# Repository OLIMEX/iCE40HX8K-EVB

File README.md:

# iCE40HX8K-EVB
iCE40HX8K development board with SRAM and bus for fast ADC, DAC, IOs

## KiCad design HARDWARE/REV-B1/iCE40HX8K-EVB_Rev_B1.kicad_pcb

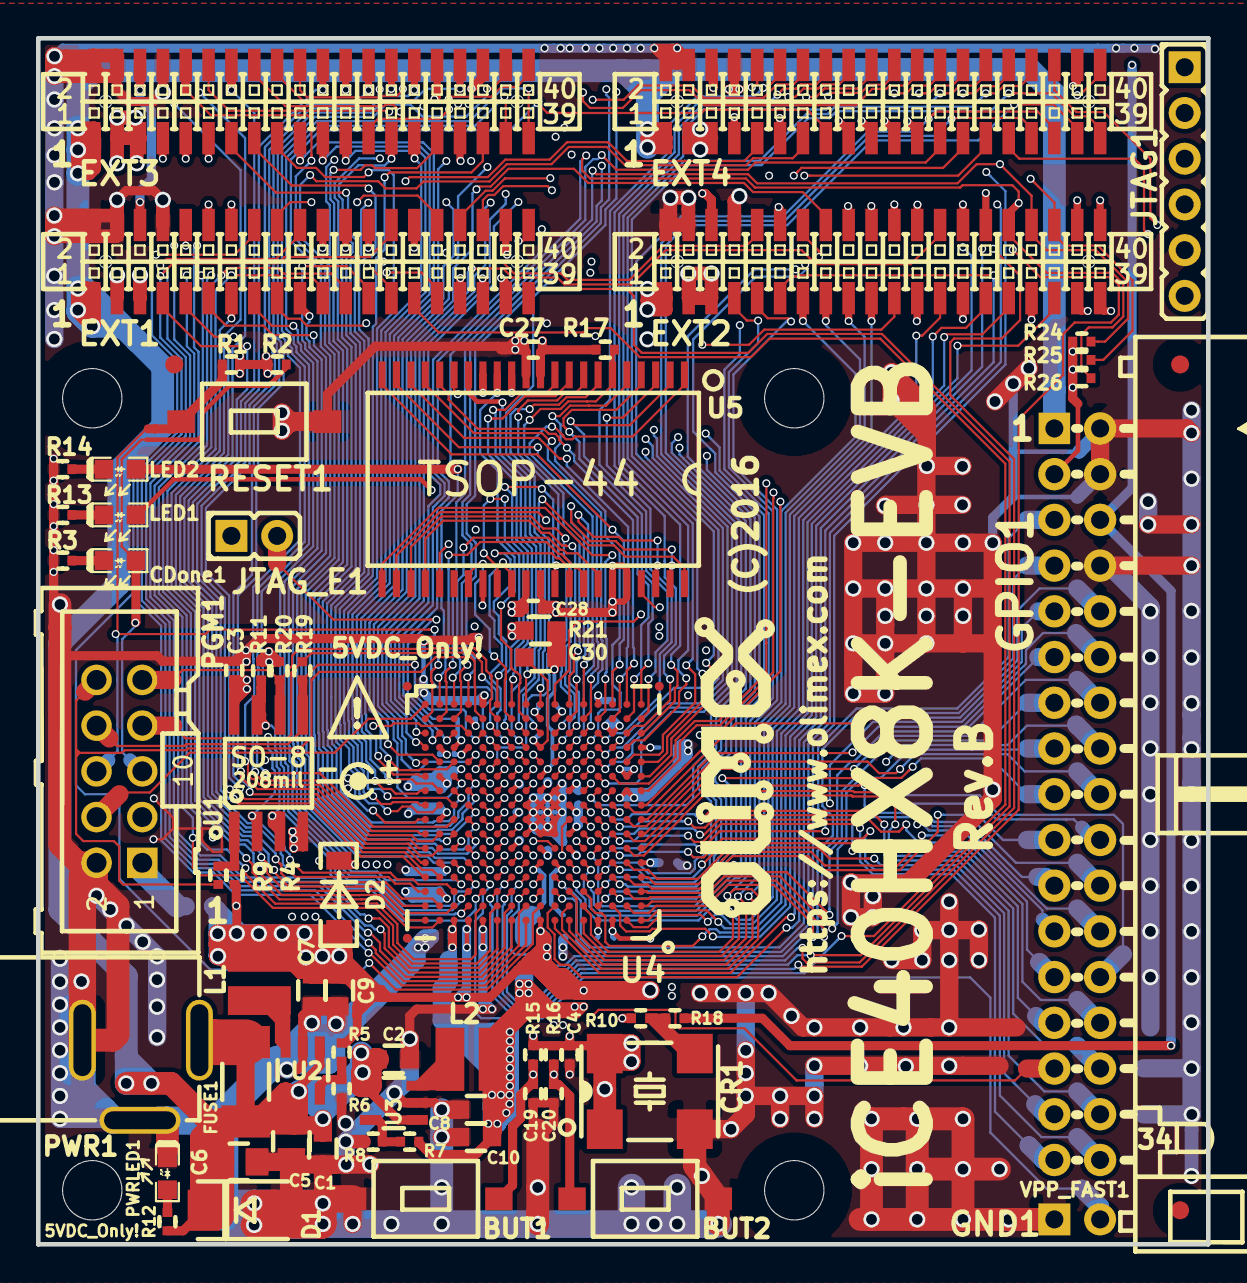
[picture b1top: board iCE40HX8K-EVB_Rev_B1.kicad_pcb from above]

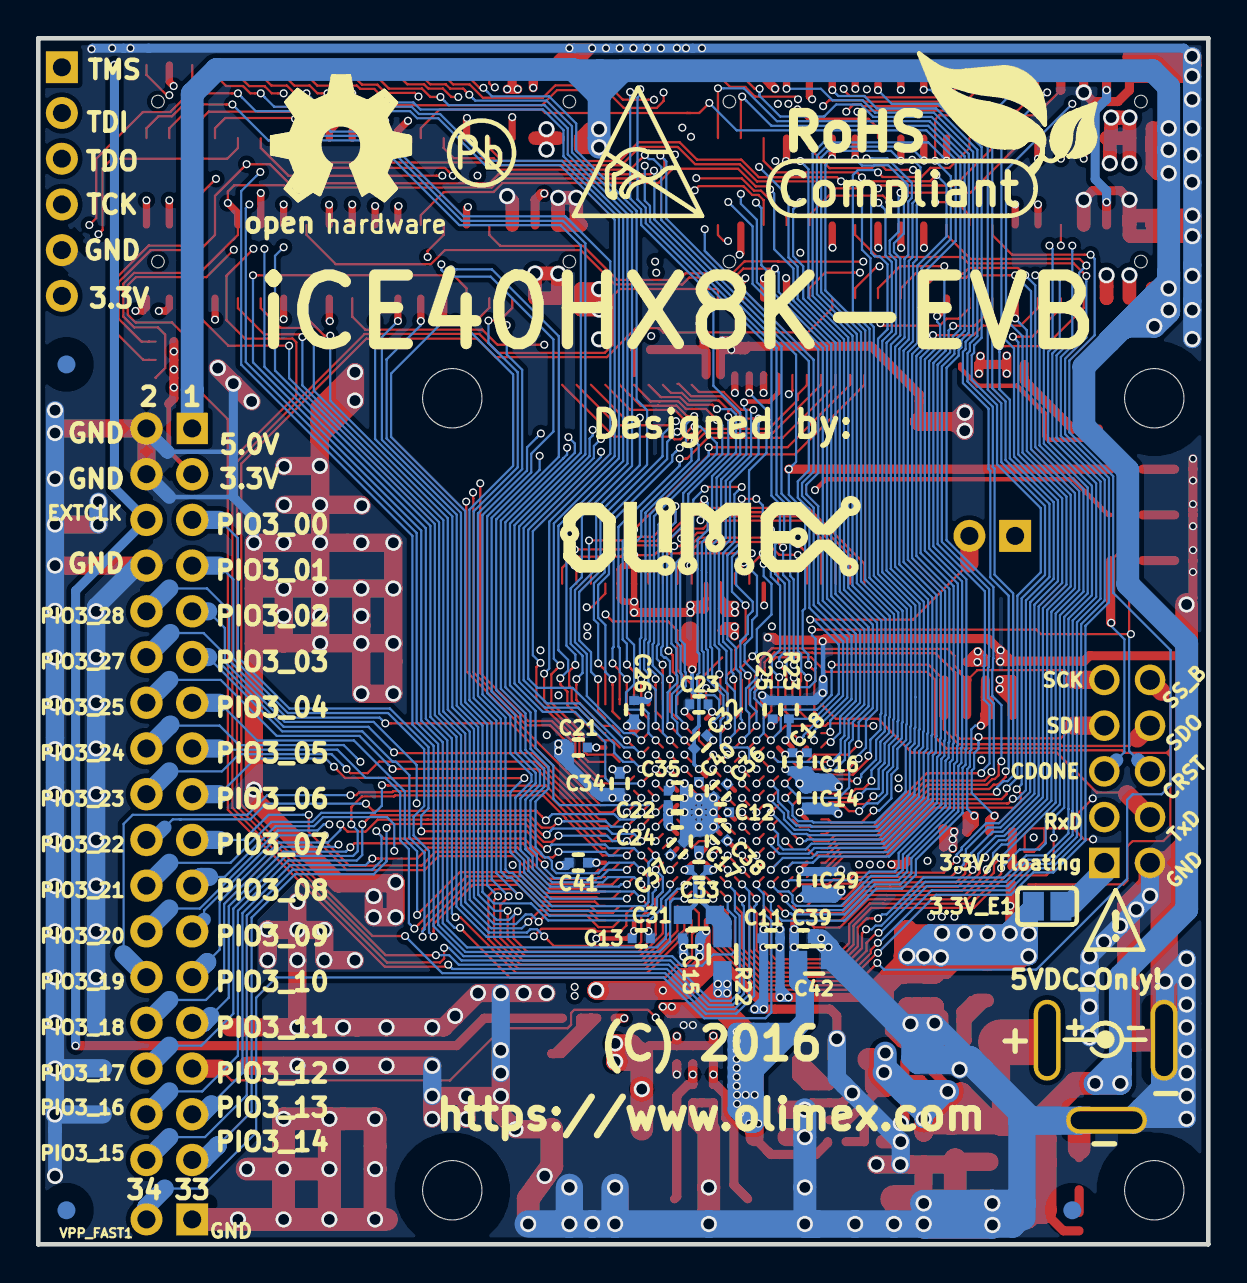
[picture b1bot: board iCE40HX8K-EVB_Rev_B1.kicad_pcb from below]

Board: 4 copper layers, 65.0 x 67.0 mm, 104 parts (32 on the bottom side), 232 nets.

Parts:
3.3V_E1: Opened; SJ
BUT1, BUT2: T1107A(6x3,8x2,5MM)
C1, C2, C7, C8, C9, C10, C30, C31, C42: 22uF/6.3V/20%/X5R; C_0603_5MIL_DWS
C3, C4, C11, C12, C13, C14, C15, C16, C17, C18, C21, C22, C23, C24, C25, C26, C27, C28, C29, C32, C33, C34, C35, C36, C37, C38, C39, C40, C41: 100nF/50V/20%/Y5V; C_0402_5MIL_DWS
C5, C6: 47uF/6.3V/20%/X5R; C_0805_5MIL_DWS
C19, C20: NA(100nF/50V/20%/Y5V); C_0402_5MIL_DWS
CDone1: LED/Green/0603; LED_0603_KA
CR1: Oscillator-100MHZ_TXC-7W; Oscillator_7.0x5.0mm
D1: SMBJ6.0A(DO-214AA); DO214AA_1(K)-2(A)
D2: 1N5819(S4SOD-123); SOD-123_1C-2A_KA
EXT1, EXT2, EXT3, EXT4: PA-V16X-2X20-LF; GPH127SMT-02X20(PA-V16X-2X20-LF)
FUSE1: NA(5025); FUSE-5025
GND1: TESTPAD; TEST_PAD40x70_SQUARE
GPIO1: BH34R
JTAG1: NA(HN1x6); HN1x6
JTAG_E1: NA(HN1x2(Opened)); HN1x2
L1, L2: 2.2uH/1.5A/DCR<0.1R/CD32; CD32
LED1, LED2: LED/Red/0603; LED_0603_KA
MountingHole: Mounting_hole_3.3mm
MountingHole#2, MountingHole#3, MountingHole#4: Mounting_hole_3.3mm
PGM1: BH10S; UEXT_ML10
PWR1: PWRJ-2mm(YDJ-1134); PWRJ-2mm(YDJ-1136)
PWRLED1: LED/Red/0603; LED_0603_KA
R1, R4, R11, R15, R16, R17, R20, R23: 10k; R_0402_5MIL_DWS
R2, R12, R13, R14: 2.2k; R_0402_5MIL_DWS
R3, R9, R10, R18: 22R; R_0402_5MIL_DWS
R5, R7, R8: 4.99k/1%; R_0402_5MIL_DWS
R6: 1.1k/1%; R_0402_5MIL_DWS
R19: NA(22R); R_0402_5MIL_DWS
R21, R22: 100R; R_0603_5MIL_DWS
R24, R25, R26: NA(10k); R_0402_5MIL_DWS
RESET1: T1107A(6x3,8x2,5MM)
Ref**: Val**; LOGO_ROHS_1
Ref**#2: Val**; LOGO_ANTISTATIC_1
U1: EN25Q16B-104HIP(SOIC-8_208mil); SO-8_208mil
U2, U3: SY8009AAAC(SOT23-5); SOT-23-5
U4: iCE40HX8K-CT256(256-Ball_caBGA); 256-Ball_caBGA(Pitch_0.80mm_Pad_0.40mm)
U5: K6R4016V1D-TC10(TSOP-44); TSOP-44_Pitch-0.80mm_18.80x11.80x1.20mm
VPP_FAST1: TESTPAD; TEST_PAD_40x70_Round

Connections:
+1V2: C8.2, C10.2, C34.2, C35.2, C36.2, C37.2, C38.2, C39.2, C42.1, L2.1, R7.2, R21.2, R22.2, U4.A14, U4.F6, U4.F10, U4.K6, U4.K10, U4.L2
+3V3: 3.3V_E1.2, C3.2, C4.2, C7.2, C9.2, C11.2, C12.2, C13.2, C14.2, C15.2, C16.2, C17.2, C18.1, C21.2, C22.2, C23.2, C24.2, C25.2, C26.2, C27.2, C28.2, C29.2, C40.2, C41.2, CR1.1, CR1.4, D2.2, EXT1.3, EXT1.5, EXT2.3, EXT2.5, EXT3.3, EXT3.5, EXT4.3, EXT4.5, GPIO1.3, JTAG1.6, JTAG_E1.1, L1.1, R1.2, R2.2, R4.2, R5.2, R11.1, R15.2, R16.2, R17.1, R20.2, R24.1, R25.1, R26.1, U1.8, U4.A3, U4.A8, U4.A13, U4.C15, U4.E1, U4.F8, U4.G6, U4.H10, U4.H15, U4.J6, U4.K8, U4.N1, U4.N13, U4.N15, U4.P3, U4.R8, U4.R13, U5.11, U5.33
+5V: C1.2, C2.2, C5.2, C6.2, D1.1, EXT1.1, EXT2.1, EXT3.1, EXT4.1, FUSE1.1, FUSE1.2, GPIO1.1, PWR1.+, R12.1, U2.1, U2.4, U3.1, U3.4
/EXTCLK: EXT1.6, EXT2.6, EXT3.6, EXT4.6, GPIO1.6, R18.1
/PIO0_00: EXT1.7, U4.C14
/PIO0_01: EXT1.9, U4.B15
/PIO0_02: EXT1.11, U4.D13
/PIO0_03: EXT1.13, U4.B14
/PIO0_04: EXT1.15, U4.C12
/PIO0_05: EXT1.17, U4.E11
/PIO0_06: EXT1.19, U4.C13
/PIO0_07: EXT1.21, U4.A16
/PIO0_08: EXT1.23, U4.A15
/PIO0_09: EXT1.25, U4.B13
/PIO0_10: EXT1.27, U4.E10
/PIO0_11: EXT1.29, U4.C11
/PIO0_12: EXT1.31, U4.D11
/PIO0_13: EXT1.33, U4.B12
/PIO0_14: EXT1.35, U4.B10
/PIO0_15: EXT1.37, U4.B11
/PIO0_16: EXT1.39, U4.C10
/PIO0_17: EXT1.40, U4.A10
/PIO0_18: EXT1.38, U4.A11
/PIO0_19: EXT1.36, U4.D10
/PIO0_20: EXT1.34, U4.C9
/PIO0_21: EXT1.32, U4.E9
/PIO0_22: EXT1.30, U4.D9
/PIO0_23: EXT1.28, U4.A9
/PIO0_24: EXT1.26, U4.F9
/PIO0_25: EXT1.24, U4.C8
/PIO0_26: EXT1.22, U4.F7
/PIO0_27: EXT1.20, U4.B9
/PIO0_28: EXT1.18, U4.D8
/PIO0_29: EXT1.16, U4.B8
/PIO0_30: EXT1.14, U4.A7
/PIO0_31: EXT1.12, U4.C7
/PIO0_32: EXT1.10, U4.B7
/PIO0_33: EXT2.7, U4.B6
/PIO0_34: EXT2.9, U4.C6
/PIO0_35: EXT2.11, U4.D7
/PIO0_36: EXT2.13, U4.A6
/PIO0_37: EXT2.15, U4.D6
/PIO0_38: EXT2.17, U4.A5
/PIO0_39: EXT2.19, U4.B5
/PIO0_40: EXT2.21, U4.E6
/PIO0_41: EXT2.23, U4.B4
/PIO0_42: EXT2.25, U4.A2
/PIO0_43: EXT2.27, U4.D5
/PIO0_44: EXT2.29, U4.A1
/PIO0_45: EXT2.31, U4.C5
/PIO0_46: EXT2.33, U4.C4
/PIO0_47: EXT2.35, U4.B3
/PIO0_48: EXT2.37, U4.D4
/PIO0_49: EXT2.39, U4.E5
/PIO0_50: EXT2.40, U4.D3
/PIO0_51: EXT2.38, U4.C3
/PIO1_00: EXT2.36, JTAG1.2, R25.2, U4.R14
/PIO1_01: EXT2.34, JTAG1.1, R24.2, U4.R15
/PIO1_02: EXT2.32, JTAG1.4, R26.2, U4.P14
/PIO1_03: EXT2.30, JTAG1.3, U4.P15
/PIO1_04: EXT2.28, U4.P16
/PIO1_05: EXT2.26, U4.M13
/PIO1_06: EXT2.24, U4.M14
/PIO1_07: EXT2.22, U4.L12
/PIO1_08: EXT2.20, U4.N16
/PIO1_09: EXT2.18, U4.L13
/PIO1_10: EXT2.16, U4.L14
/PIO1_11: EXT2.14, U4.K12
/PIO1_12: EXT2.12, U4.M16
/PIO1_13: EXT2.10, U4.J10
/PIO1_14: EXT3.7, U4.M15
/PIO1_15: EXT3.9, U4.J11
/PIO1_16: EXT3.11, U4.L16
/PIO1_17: EXT3.13, U4.K13
/PIO1_18: EXT3.15, U4.K14
/PIO1_19: EXT3.17, U4.J15
/PIO1_20: EXT3.19, U4.K15
/PIO1_21: EXT3.21, U4.K16
/PIO1_22: EXT3.23, U4.J14
/PIO1_23: EXT3.25, U4.J12
/PIO1_24: EXT3.27, U4.J13
/PIO1_25: EXT3.29, U4.J16
/PIO1_26: EXT3.31, U4.H13
/PIO1_27: EXT3.33, U4.H11
/PIO1_28: EXT3.35, U4.H16
/PIO1_29: EXT3.37, U4.H14
/PIO1_30: EXT3.39, U4.G16
/PIO1_31: EXT3.40, U4.H12
/PIO1_32: EXT3.38, U4.G15
/PIO1_33: EXT3.36, U4.G10
/PIO1_34: EXT3.34, U4.F16
/PIO1_35: EXT3.32, U4.G11
/PIO1_36: EXT3.30, U4.F15
/PIO1_37: EXT3.28, U4.G14
/PIO1_38: EXT3.26, U4.E16
/PIO1_39: EXT3.24, U4.G13
/PIO1_40: EXT3.22, U4.D16
/PIO1_41: EXT3.20, U4.G12
/PIO1_42: EXT3.18, U4.F14
/PIO1_43: EXT3.16, U4.F12
/PIO1_44: EXT3.14, U4.D15
/PIO1_45: EXT3.12, U4.F11
/PIO1_46: EXT3.10, U4.E14
/PIO1_47: EXT4.7, U4.C16
/PIO1_48: EXT4.9, U4.F13
/PIO1_49: EXT4.11, U4.B16
/PIO1_50: EXT4.13, U4.E13
/PIO1_51: EXT4.15, U4.D14
/PIO2_37: EXT4.17, U4.M11
/PIO2_38: EXT4.19, U4.T13
/PIO2_39: EXT4.21, U4.N12
/PIO2_40/RxD: PGM1.3, U4.L11
/PIO2_41/TxD: PGM1.4, U4.T16
/PIO2_42/LED1: EXT4.23, LED1.2, U4.M12
/PIO2_43/LED2: EXT4.25, LED2.2, U4.R16
/PIO2_44/BUT1: BUT1.1, C19.2, R15.1, U4.K11
/PIO2_45/BUT2: BUT2.1, C20.2, R16.1, U4.P13
/PIO3_00/IOL_1A: GPIO1.5, U4.E4
/PIO3_01/IOL_1B: GPIO1.7, U4.B2
/PIO3_02/IOL_2A: GPIO1.9, U4.F5
/PIO3_03/IOL_2B: GPIO1.11, U4.B1
/PIO3_04/IOL_3A: GPIO1.13, U4.C1
/PIO3_05/IOL_3B: GPIO1.15, U4.C2
/PIO3_06/IOL_4A: GPIO1.17, U4.F4
/PIO3_07/IOL_4B: GPIO1.19, U4.D2
/PIO3_08/IOL_5A: GPIO1.21, U4.G5
/PIO3_09/IOL_5B: GPIO1.23, U4.D1
/PIO3_10/IOL_6A: GPIO1.25, U4.G4
/PIO3_11/IOL_6B: GPIO1.27, U4.E3
/PIO3_12/IOL_7A: GPIO1.29, U4.H5
/PIO3_13/IOL_7B: GPIO1.31, U4.E2
/PIO3_14/IOL_8A: GPIO1.33, U4.G3
/PIO3_15/IOL_8B: GPIO1.34, U4.F3
/PIO3_16/IOL_9A: GPIO1.32, U4.H3
/PIO3_17/IOL_9B: GPIO1.30, U4.F2
/PIO3_18/IOL_10A: GPIO1.28, U4.H6
/PIO3_19/IOL_10B: GPIO1.26, U4.F1
/PIO3_20/IOL_11A: GPIO1.24, U4.H4
/PIO3_21/IOL_11B: GPIO1.22, U4.G2
/PIO3_22/IOL_12A: GPIO1.20, U4.J4
/PIO3_23/IOL_12B: GPIO1.18, U4.H2
/PIO3_24/IOL_13A: GPIO1.16, U4.J5
/PIO3_25/IOL_13B: GPIO1.14, U4.G1
/PIO3_27/IOL_14B: GPIO1.12, U4.H1
/PIO3_28/IOL_15A: GPIO1.10, U4.J2
/PIO3_29: EXT4.27, U4.J1
/PIO3_30: EXT4.29, U4.K1
/PIO3_31: EXT4.31, U4.K3
/PIO3_32: EXT4.33, U4.L4
/PIO3_33: EXT4.35, U4.L1
/PIO3_34: EXT4.37, U4.K4
/PIO3_35: EXT4.39, U4.M1
/PIO3_36: EXT4.40, U4.L6
/PIO3_37: EXT4.38, U4.L3
/PIO3_38: EXT4.36, U4.K5
/PIO3_39: EXT4.34, U4.M2
/PIO3_40: EXT4.32, U4.L7
/PIO3_41: EXT4.30, U4.N2
/PIO3_42: EXT4.28, U4.M6
/PIO3_43: EXT4.26, U4.M3
/PIO3_44: EXT4.24, U4.L5
/PIO3_45: EXT4.22, U4.N3
/PIO3_46: EXT4.20, U4.P1
/PIO3_47: EXT4.18, U4.M4
/PIO3_48: EXT4.16, U4.P2
/PIO3_49: EXT4.14, U4.M5
/PIO3_50: EXT4.12, U4.R1
/PIO3_51: EXT4.10, U4.N4
/SA0: U4.N6, U5.1
/SA1: U4.T1, U5.2
/SA2: U4.P4, U5.3
/SA3: U4.R2, U5.4
/SA4: U4.N5, U5.5
/SA5: U4.T2, U5.18
/SA6: U4.P5, U5.19
/SA7: U4.R3, U5.20
/SA8: U4.R5, U5.21
/SA9: U4.T3, U5.22
/SA10: U4.R4, U5.23
/SA11: U4.M7, U5.24
/SA12: U4.N7, U5.25
/SA13: U4.P6, U5.26
/SA14: U4.M8, U5.27
/SA15: U4.T5, U5.42
/SA16: U4.R6, U5.43
/SA17: U4.P8, U5.44
/SD0: U4.T8, U5.7
/SD1: U4.P7, U5.8
/SD2: U4.N9, U5.9
/SD3: U4.T9, U5.10
/SD4: U4.M9, U5.13
/SD5: U4.R9, U5.14
/SD6: U4.K9, U5.15
/SD7: U4.P9, U5.16
/SD8: U4.R10, U5.29
/SD9: U4.L10, U5.30
/SD10: U4.P10, U5.31
/SD11: U4.N10, U5.32
/SD12: U4.T10, U5.35
/SD13: U4.T11, U5.36
/SD14: U4.T15, U5.37
/SD15: U4.T14, U5.38
/SRAM_#CS: R17.2, U4.T6, U5.6
/SRAM_#OE: U4.L9, U5.41
/SRAM_#WE: U4.T7, U5.17
/SYSCLK: R10.1, U4.J3
/TRST_B: JTAG_E1.2, R23.1, U4.N14
/iCE40-CDONE: CDone1.2, PGM1.5, R2.1, U4.M10
/iCE40-CRESET: PGM1.6, R1.1, RESET1.1, U4.N11
/iCE40-SCK: PGM1.9, R20.1, U1.6, U4.R11
/iCE40-SDI: PGM1.7, R19.1, U1.2, U4.P11
/iCE40-SDO: PGM1.8, R19.2, U1.5, U4.P12
/iCE40-SS_B: PGM1.10, R9.1, U4.R12
GND: BUT1.2, BUT2.2, C1.1, C2.1, C3.1, C4.1, C5.1, C6.1, C7.1, C8.1, C9.1, C10.1, C11.1, C12.1, C13.1, C14.1, C15.1, C16.1, C17.1, C18.2, C19.1, C20.1, C21.1, C22.1, C23.1, C24.1, C25.1, C26.1, C27.1, C28.1, C29.1, C34.1, C35.1, C36.1, C37.1, C38.1, C39.1, C40.1, C41.1, C42.2, CR1.2, D1.2, EXT1.2, EXT1.4, EXT1.8, EXT2.2, EXT2.4, EXT2.8, EXT3.2, EXT3.4, EXT3.8, EXT4.2, EXT4.4, EXT4.8, GND1.1, GPIO1.2, GPIO1.4, GPIO1.8, JTAG1.5, PGM1.2, PWR1.-, PWRLED1.1, R3.2, R6.2, R8.2, R13.2, R14.2, R23.2, RESET1.2, U1.4, U2.2, U3.2, U4.A4, U4.A12, U4.E15, U4.G7, U4.G8, U4.G9, U4.H7, U4.H8, U4.H9, U4.J7, U4.J8, U4.J9, U4.K2, U4.K7, U4.L15, U4.R7, U4.T4, U4.T12, U5.12, U5.34, U5.39, U5.40
unnamed: 3.3V_E1.1, PGM1.1
unnamed: C30.1, C32.2, R21.1, U4.L8
unnamed: C30.2, C32.1, U4.N8
unnamed: C31.1, C33.2, R22.1, U4.E8
unnamed: C31.2, C33.1, U4.E7
unnamed: CDone1.1, R3.1
unnamed: CR1.3, R10.2, R18.2
unnamed: D2.1, U4.E12
unnamed: L1.2, U2.3
unnamed: L2.2, U3.3
unnamed: LED1.1, R13.1
unnamed: LED2.1, R14.1
unnamed: PWRLED1.2, R12.2
unnamed: R4.1, R9.2, U1.1
unnamed: R5.1, R6.1, U2.5
unnamed: R7.1, R8.1, U3.5
unnamed: R11.2, U1.3, U1.7
unnamed: U4.D12, VPP_FAST1.1

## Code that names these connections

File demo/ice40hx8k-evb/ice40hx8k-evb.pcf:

set_io CLK J3
set_io BUT1 K11
set_io BUT2 P13
set_io LED1 M12
set_io LED2 R16

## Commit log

2017-06-22 iCE40HX8K-EVB Rev.B CAD files
2017-08-23 Add the LEDs blink demo for this evaluation board
2017-08-23 Add the VGA demo for this evaluation board
2021-01-03 Switch to NextPNR
2021-09-16 Update
    Revision B1
2024-10-10 Switch examples to use `nextpnr-ice40` instead of deprecated `arachne-pnr`
    - Also updated gitignore files to include new output generated json file
2026-05-23 Update README
    renamed 1K to 8K

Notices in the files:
HARDWARE/REV-B1/iCE40HX8K-EVB_Rev_B1.kicad_pcb:
(C)2016
